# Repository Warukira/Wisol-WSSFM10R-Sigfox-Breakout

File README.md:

## Wisol WSSFM10R Sigfox Breakout Board

This breakout board connects your Arduino, Raspberry Pi and other devices to the Sigfox IoT network for low-power, long-range communications. The board uses the Wisol WSSFM10Rx module to connect to the Sigfox network. The interface between the device and the breakout board is based on UART Serial I/O at 9600 bps with 4 pins (3.3V, GND, TX, RX). A U.FL antenna and a Sigfox network subscription are required.

Refer to the `Hardware` folder.

- Autodesk EAGLE board and schematic for Wisol WSSFM10R2/4 Sigfox Breakout board (Sigfox Zones RCZ2 and RCZ4)

- Formatted for Seeed Fusion PCB Assembly service, so that you may submit the files from this repository and order the breakout board fully assembled with the onboard components, including the Wisol Sigfox module: <br>
  https://www.seeedstudio.com/fusion.html

- All components sourced from Seeed Open Parts Library (except for Wisol module) for quicker PCB assembly by Seeed Fusion: <br>
  https://www.seeedstudio.com/opl.html

- Original design by Sea Slug Labs: <br>
  https://github.com/SeaSlugLabs/Wisol-WSSFM10R2-Sigfox-Breakout
  
- Why I created the breakout board: <br>
  https://medium.com/@ly.lee/making-my-first-ever-pcb-with-seeed-fusion-pcb-assembly-service-9af5736016b3

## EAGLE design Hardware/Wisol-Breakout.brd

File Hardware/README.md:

## Wisol WSSFM10R Sigfox Breakout Board

This breakout board connects your Arduino, Raspberry Pi and other devices to the Sigfox IoT network for low-power, long-range communications. The board uses the Wisol WSSFM10Rx module to connect to the Sigfox network. The interface between the device and the breakout board is based on UART Serial I/O at 9600 bps with 4 pins (3.3V, GND, TX, RX). A U.FL antenna and a Sigfox network subscription are required.

- Autodesk EAGLE board and schematic for Wisol WSSFM10R2/4 Sigfox Breakout board (Sigfox Zones RCZ2 and RCZ4) are in `Wisol-Breakout.brd` and `Wisol-Breakout.sch`

- The PCB design uses 4 layers. If you're using the Free Edition of Autodesk EAGLE, you will only see the top and bottom layers.
  Subscribe to the Standard Edition of Autodesk EAGLE to see all 4 layers.

- Formatted for Seeed Fusion PCB Assembly service, so that you may submit the files from this repository and order the breakout board fully assembled with the onboard components, including the Wisol Sigfox module: <br>
  https://www.seeedstudio.com/fusion.html

- All components sourced from Seeed Open Parts Library (except for Wisol module) for quicker PCB assembly by Seeed Fusion: <br>
  https://www.seeedstudio.com/opl.html

- PCB layout was validated in Autodesk EAGLE with the Seeed Fusion Design Rules `SeeedStudio_4layer_DRU_no_angle_20140221.dru`

- PCB design was exported from Autodesk EAGLE to Seeed Fusion in Gerber RS-274x and Excellon (drill) formats using the CAM Processor `Seeed_Gerber_Generater_4-layer_1-2-15-16.cam`

## Seeed Fusion PCB Manufacturing and Assembly

Order submitted to Seeed Fusion for PCB manufacturing and assembly at https://www.seeedstudio.com/fusion_pcb.html:

1. `Wisol-Breakout_2018-xx-xx.zip`: PCB design in Gerber RS-274x and Excellon (drill) formats

1. PCB Specifications: <br>
  PCB Dimensions - 25.4mm*21.6mm <br>
  Impedance Control - No <br>
  Surface Finish - HASL <br>
  Minimum Solder Mask Dam - 0.4mm↑ <br>
  Copper Weight - 1oz. <br>
  Plated Half-holes / Castellated Holes - No <br>
  Minimum Drill Hole Size - 0.3mm <br>
  PCB Color - Green <br>
  Base Material - FR-4 TG130 <br>
  No. of Layers - 4 layers <br>
  Blind or Buried Vias - No <br>
  PCB Thickness - 1.6 <br>
  Trace Width / Spacing - 4/4 mil <br>
  No. of Different Designs - 1 <br>

1. `Wisol-Breakout-BOM.csv`: Bill Of Materials (BOM) for Sigfox Zone RCZ4. Update the WSSFM10R Manufacturer Part Number (MPN) in the BOM if you are in other zones: <br>
  For RCZ1: WSSFM10R1AT<br>
  For RCZ2: WSSFM10R2AT<br>
  For RCZ3: WSSFM10R3AT<br>
  For RCZ4: WSSFM10R4AT<br>

1. Link provided to Seeed Fusion for sourcing WSSFM10R4AT (RCZ4): <br>																									
  https://www.avnet.com/shop/apac/products/wisol/wssfm10r4at-3074457345633583729/?aka_re=1																							

## Changes for Sigfox Zones RCZ1 and RCZ3

The design here was created for Wisol WSSFM10R2 and R4 (Sigfox Zones RCZ2 and RCZ4). For Wisol WSSFM10R1 and R3 (Sigfox Zones RCZ1 and RCZ3) the footprint is smaller and the module needs to be moved down by 5mm.  All other pins and components are unchanged.

## InnoComm Sigfox Breakout Board

I have created another breakout board for the InnoComm Sigfox module SN10-12:

https://github.com/lupyuen/innocomm-sigfox-breakout

## References

1. Original PCB design by Sea Slug Labs: <br>
  https://github.com/SeaSlugLabs/Wisol-WSSFM10R2-Sigfox-Breakout
  
1. Why I created the breakout board: <br>
  https://medium.com/@ly.lee/making-my-first-ever-pcb-with-seeed-fusion-pcb-assembly-service-9af5736016b3
  
1. List of all Sigfox Zones and the countries covered: <br>
  http://makers.sigfox.com/about/

1. Wisol WSSFM10R H/W Design Guide R03 170320

1. Wisol WSSFM10R4AT Datasheet REV02 170320

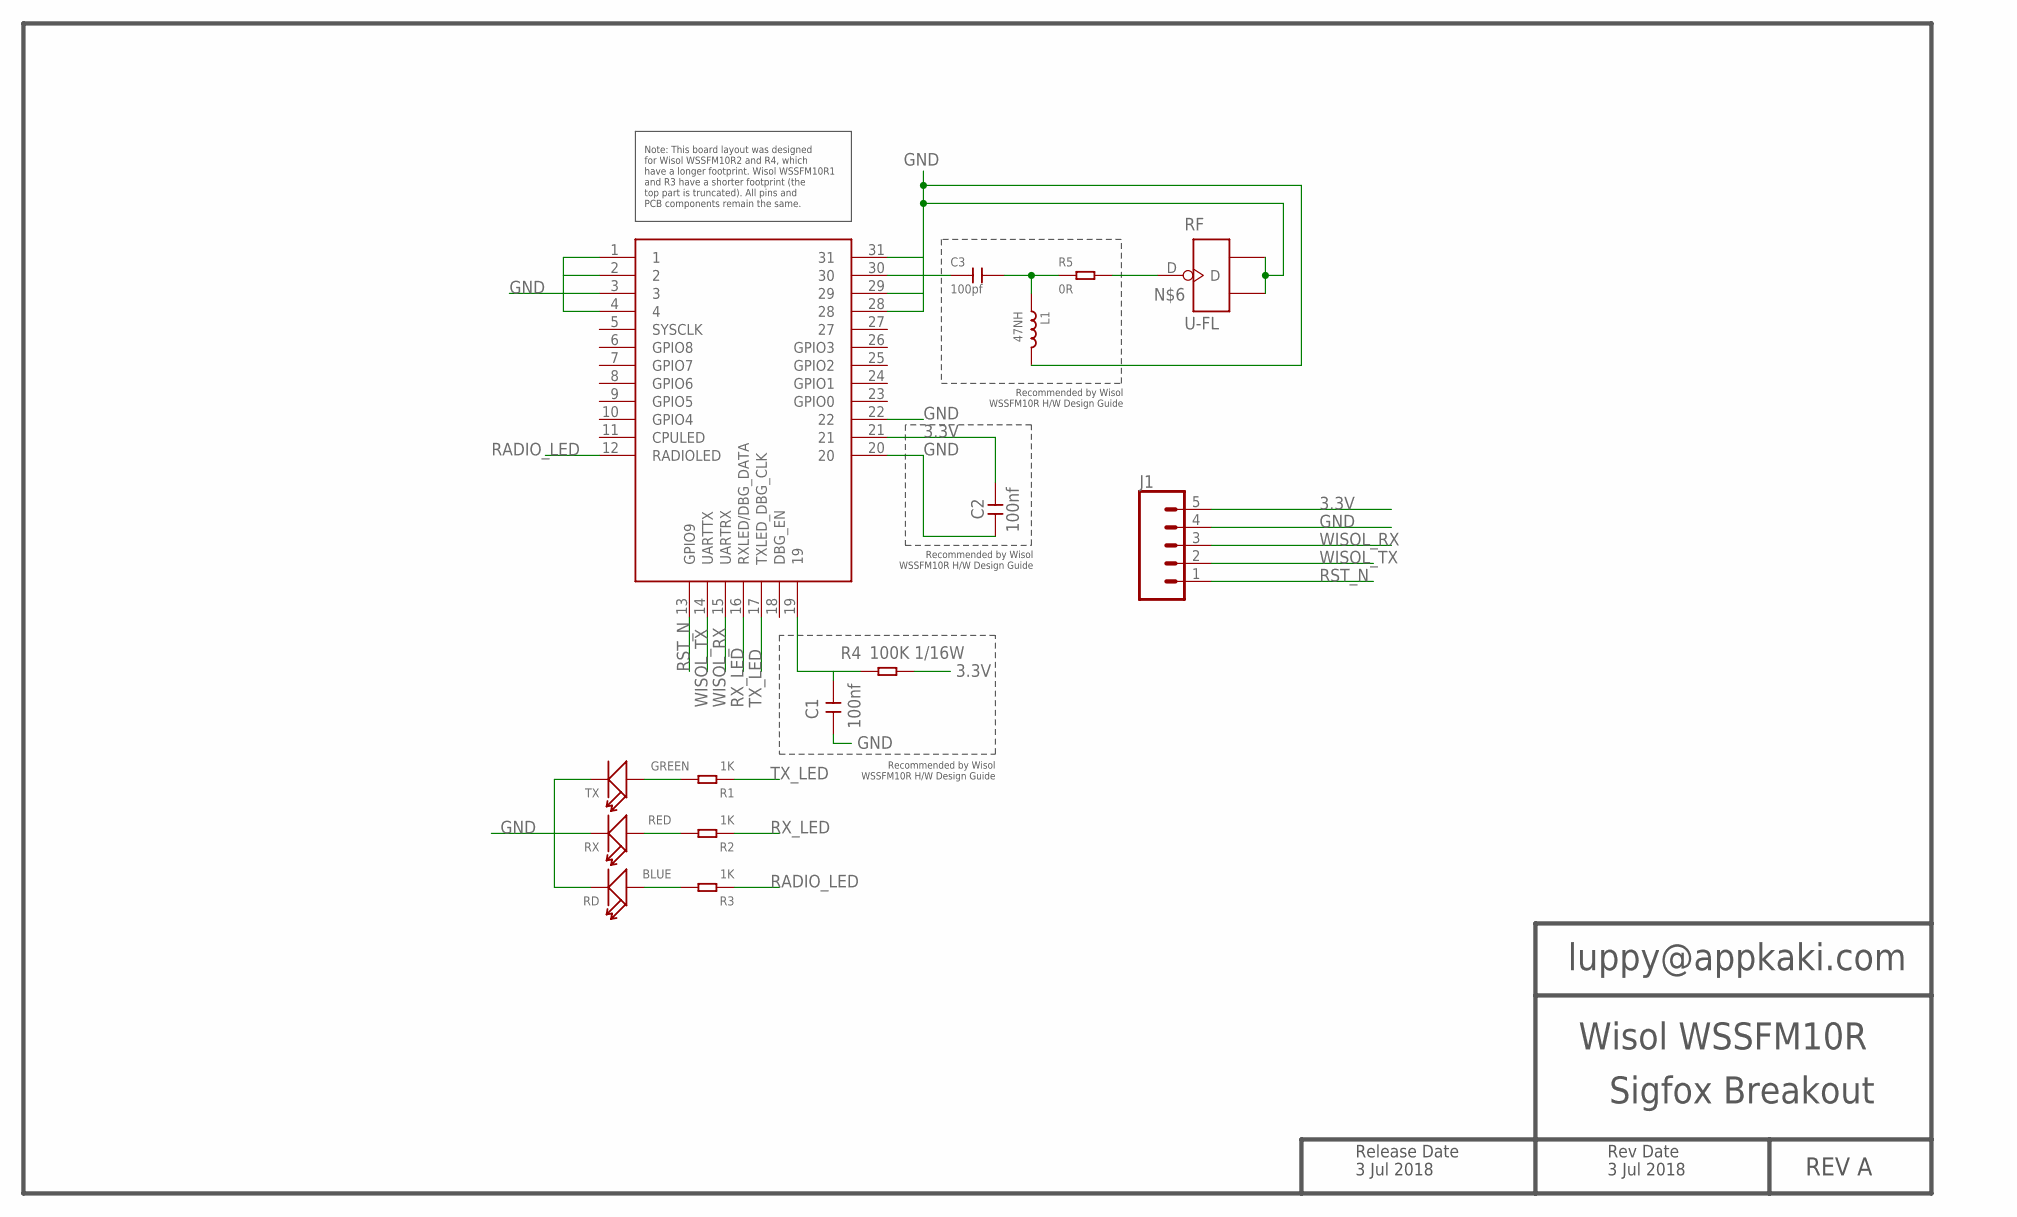
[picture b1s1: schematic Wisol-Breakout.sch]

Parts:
C1, C2: 100nf; C0402
C3: 100pf; C0402
J1: CONN_05; 1X05
L1: 47NH; L0402; MPN LQW15AN47NJ00D
R1, R2, R3: 1K; R0402; MPN RC0402FR-071KL
R4: 100K 1/16W; R0402
R5: 0R; R0402
RD: BLUE; LED-0603
RF: U-FL; U-FL3P-SMD-2.6X2.6X1.0MM
RX: RED; LED-0603
TX: GREEN; LED-0603
WSSFM10R: WSSFM10RWSSFM10R2R4; WSSFM10R

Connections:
3.3V: C2.2, J1.5, R4.2, WSSFM10R.21
GND: C1.1, C2.1, J1.4, L1.2, RD.-, RF.GND1, RF.GND2, RX.-, TX.-, WSSFM10R.1, WSSFM10R.2, WSSFM10R.3, WSSFM10R.4, WSSFM10R.20, WSSFM10R.22, WSSFM10R.28, WSSFM10R.29, WSSFM10R.31
unnamed: C1.2, R4.1, WSSFM10R.19
unnamed: R1.2, TX.+
unnamed: R2.2, RX.+
unnamed: R3.2, RD.+
unnamed: C3.2, L1.1, R5.1
unnamed: R5.2, RF.D
RADIO_LED: R3.1, WSSFM10R.12 (RADIOLED)
RF_OUT: C3.1, WSSFM10R.30
RST_N: J1.1, WSSFM10R.13 (GPIO9)
RX_LED: R2.1, WSSFM10R.16 (RXLED/DBG_DATA)
TX_LED: R1.1, WSSFM10R.17 (TXLED_DBG_CLK)
WISOL_RX: J1.3, WSSFM10R.15 (UARTRX)
WISOL_TX: J1.2, WSSFM10R.14 (UARTTX)

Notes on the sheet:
luppy@appkaki.com
Wisol WSSFM10R
REV A
Sigfox Breakout
Release Date
3 Jul 2018
Rev Date
Note: This board layout was designed for Wisol WSSFM10R2 and R4, which have a longer footprint. Wisol WSSFM10R1 and R3 have a shorter footprint (the top part is truncated). All pins and PCB components remain the same.
Recommended by Wisol WSSFM10R H/W Design Guide

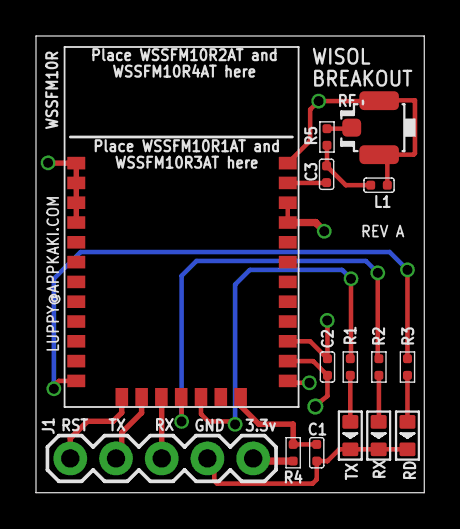
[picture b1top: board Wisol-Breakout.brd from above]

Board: 4 copper layers, 21.6 x 25.4 mm, 15 parts (0 on the bottom side), 15 nets.

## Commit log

2017-05-05 Create Hardware
2017-05-05 Add Hardware Files
2017-05-29 Arduino Local Test
2017-05-29 Arduino Local Receive Test
2017-07-23 Program to send temperature of the wisol
    Program to send the temperature over the sigfox network.
2017-08-10 Adding command AT$RC
2018-07-02 Rename WisolWSSFM10R2-Breakout.brd to Wisol-Breakout.brd
2018-07-02 Rename WisolWSSFM10R2-Breakout.sch to Wisol-Breakout.sch
2018-07-02 Updated for Seeed PCB Assembly
2018-07-02 Added Seeed DRU and Gerber Generator
2018-07-03 Added RF inductor as recommended by Wisol H/W Design Guide
2018-07-03 Added revision
2018-07-04 Updated footprint for Wisol WSSFM10R1, R3
2018-07-04 Added instructions for placement of WSSFM10R1 and R3
2018-07-04 Updated Wisol footprint
2018-07-04 Added list of Sigfox zones
2018-07-04 Added annotations for Wisol WSSFM10R H/W Design Guide
2018-07-04 Added order confirmation
2018-07-26 Shortage of Wisol Sigfox Module

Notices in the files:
parts and their libraries:
SparkFun-Connectors: Licensing: Creative Commons ShareAlike 4.0 International - https://creativecommons.org/licenses/by-sa/4.0
